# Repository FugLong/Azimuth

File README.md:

<div align="center">

</div>

# Azimuth

Azimuth is a **DIY head tracker** for flight sims, racing, and anything that works with [OpenTrack](https://github.com/opentrack/opentrack). It pairs a small **ESP32** board with a **BNO08x-class** IMU so you get stable orientation without a closed commercial device. This repo has **firmware**, **PCB** designs, **3D** plans, and **documentation**—build it, change it, or fix it yourself.

### Hardware paths

Two supported builds—same core tracker firmware where both apply; use the row that matches what you assembled.

| Path | What it is | Status |
|------|------------|--------|
| **DIY (XIAO + BNO08x)** | **Seeed XIAO ESP32-C3** + **BNO08x** breakout on **SPI** — breadboard or hand-wired. Default **`azimuth_main_diy`**; selected by default in the [**web flasher**](https://fuglong.github.io/Azimuth/). | **Ready** — tracking, Wi‑Fi, portal, USB Hatire, OpenTrack UDP. |
| **Integrated PCB** | [**`kicad/Azimuth_Design`**](kicad/Azimuth_Design/): **ESP32-C3** module, **BNO086**, RGB, buzzer, button. **`azimuth_main_pcb`**; available in the web flasher hardware selector. | **V0.1** — KiCad **ERC/DRC** clean; **assembled boards in hand**, **bring-up and testing in progress**. Same app as DIY — [roadmap](docs/roadmap.md). |

[**docs/wiring.md**](docs/wiring.md) (pinouts) · [**docs/hardware-profiles.md**](docs/hardware-profiles.md) (PlatformIO / GPIO) · [**docs/parts-list.md**](docs/parts-list.md) (sourcing — DIY store links + PCB BOM)

---

### Get started

| | |
|:---|:---|
| **Install or update firmware (USB)** | [**Web flasher**](https://fuglong.github.io/Azimuth/) (**Chrome** / **Edge**). **First flash on a bare custom PCB?** [**Copy/paste USB guide**](docs/first-usb-flash.md) (one time; web/OTA after that). |
| **Update firmware over Wi‑Fi** | Open the portal, hit **Install over Wi‑Fi** in the **Device** card or update banner — *or* hold **FUNC** for ~2 s on the PCB. The chip pulls the latest **official** build from the same GitHub Pages release URL (HTTPS) and reboots into the standby OTA slot. See [**User Guide → Updates**](docs/user-guide.md#9-firmware-updates). |
| **Settings (Wi‑Fi, OpenTrack, device)** | [**http://azimuth.local:8080**](http://azimuth.local:8080) — only after the board is on your home network. First time? Connect to **Azimuth-Tracker** (**Offline Mode**) and follow the [**quick start**](docs/quickstart.md). |
| **Manual (how to use the device)** | [**docs/user-guide.md**](docs/user-guide.md) |
| **Short Wi‑Fi → OpenTrack path** | [**docs/quickstart.md**](docs/quickstart.md) |

---

<div align="center">
<table>
  <tr>
    <td align="center"></td>
    <td align="center"></td>
  </tr>
</table>
</div>

## Overview

- **OpenTrack-first** — Send motion over **Wi‑Fi (UDP)** or **USB (Hatire)**; configure most things in the on-device web UI.
- **Affordable, open stack** — Sensible parts list, KiCad project, and firmware you can build with [PlatformIO](https://platformio.org/).
- **No cloud** — No account or hosted service; setup and tracking stay on your network.
- **Successor** to [Nano33_PC_Head_Tracker](https://github.com/FugLong/Nano33_PC_Head_Tracker): same DIY spirit, but rebuilt around **ESP32** and an external fusion IMU for better results than the old Nano 33 BLE + LSM9DS1 path.

## Need to know

- **Flashing** — Browser install needs **Chrome** or **Edge** (Web Serial). If the installer offers **erase flash**, use it for a clean device (same effect as a full settings reset).
- **First Wi‑Fi setup** — Join **Azimuth-Tracker** (**Offline Mode**), open **`http://192.168.4.1`**, save your home network. Details: [**quick start**](docs/quickstart.md) · full walkthrough: [**User Guide**](docs/user-guide.md).
- **OpenTrack** — Use **either** UDP **or** Hatire as the input, not both at once. Defaults and axis mapping: [**Using Azimuth**](docs/using-azimuth.md#opentrack-on-the-pc).
- **Power, heat, tuning** — Normal for Wi‑Fi on a small module; portal **Tracking & radio** settings; full behavior + battery notes: [**Power, heat, and battery (firmware)**](docs/power-and-thermal.md).

## Documentation

| Doc | Audience |
|-----|----------|
| [**User Guide**](docs/user-guide.md) | **Manual** — Wi‑Fi, portal, FUNC, OpenTrack, updates, battery, troubleshooting |
| [**Quick start**](docs/quickstart.md) | Fast path from flash to tracking over Wi‑Fi |
| [**Using Azimuth**](docs/using-azimuth.md) | Settings portal reference, OpenTrack (USB + Wi‑Fi), tips |
| [**Power, heat, and battery (firmware)**](docs/power-and-thermal.md) | Wi‑Fi power saving, portal polling, defaults; battery runtime / PCB pack polarity |
| [**Development**](docs/development.md) | Building firmware, CI, versioning, repo layout |
| [**Firmware architecture plan**](docs/firmware-architecture-plan.md) | Maintainers — module layout (**network split done**), CI, remaining refactors |
| [**I/O experience plan**](docs/io-led-buzzer-plan.md) | LED / buzzer / FUNC — pause/stasis, layered overrides, **wireless OTA** |
| [**Implementation handoff**](docs/implementation-handoff-prompt.md) | Copy-paste prompt + ordered tasks for agents / new contributors |
| [**Wiring**](docs/wiring.md) · [**Hardware profiles**](docs/hardware-profiles.md) · [**Parts / BOM**](docs/parts-list.md) · [**KiCad**](docs/kicad.md) | Pinouts (DIY + PCB), PlatformIO, BOM, KiCad |
| [**Roadmap**](docs/roadmap.md) | Progress, milestones, future work |
| [**Enclosure (Onshape CAD)**](https://cad.onshape.com/documents/fa78666ff0e219ba32d45d9f/w/679625cc5ba48f8e098cba83/e/0cd4f9cad8e872128d491b46) | Interactive 3D model — print/fit validation still in progress ([roadmap](docs/roadmap.md)) |

## Goals

- **Performance** — Low latency and stable orientation for games and desktop use.
- **Accessibility** — Easy-to-source parts and open tooling so people can build and modify their own trackers.
- **Interop** — First-class support for the same **OpenTrack** pipelines games and sims already use.
- **Evolvability** — Room for better calibration, on-device UX, and companion apps without legacy platform limits.

## Progress (toward V1)

| Area | Progress | Notes |
|------|:--------:|--------|
| Hardware / BOM | 100% | [Parts list](docs/parts-list.md) |
| Azimuth custom PCB ([`Azimuth_Design`](kicad/Azimuth_Design/)) — **V0.1** | **100%** (layout) · **units received** | Assembled boards **under test**. RGB / buzzer / FUNC in firmware for bring-up — see [wiring](docs/wiring.md) / [parts-list](docs/parts-list.md) — [roadmap](docs/roadmap.md) |
| Firmware | ~90% | Tracking + Wi‑Fi + portal + Hatire + **wireless OTA** + modular **`track_network_*`**; **battery ADC** polish and optional **`main`** layering remain — [roadmap](docs/roadmap.md) |
| 3D enclosure | ~90%+ | **Design nearly complete** — [**Onshape CAD (interactive)**](https://cad.onshape.com/documents/fa78666ff0e219ba32d45d9f/w/679625cc5ba48f8e098cba83/e/0cd4f9cad8e872128d491b46); print / fit validation still ahead |

```
Hardware/BOM   [████████████████████] 100%
PCB (V0.1)     [████████████████████] 100% design · boards received · testing
Firmware       [██████████████████░░] ~90%
Enclosure      [██████████████████░░] ~90%+ (design)
```

**Detailed roadmap:** [docs/roadmap.md](docs/roadmap.md)

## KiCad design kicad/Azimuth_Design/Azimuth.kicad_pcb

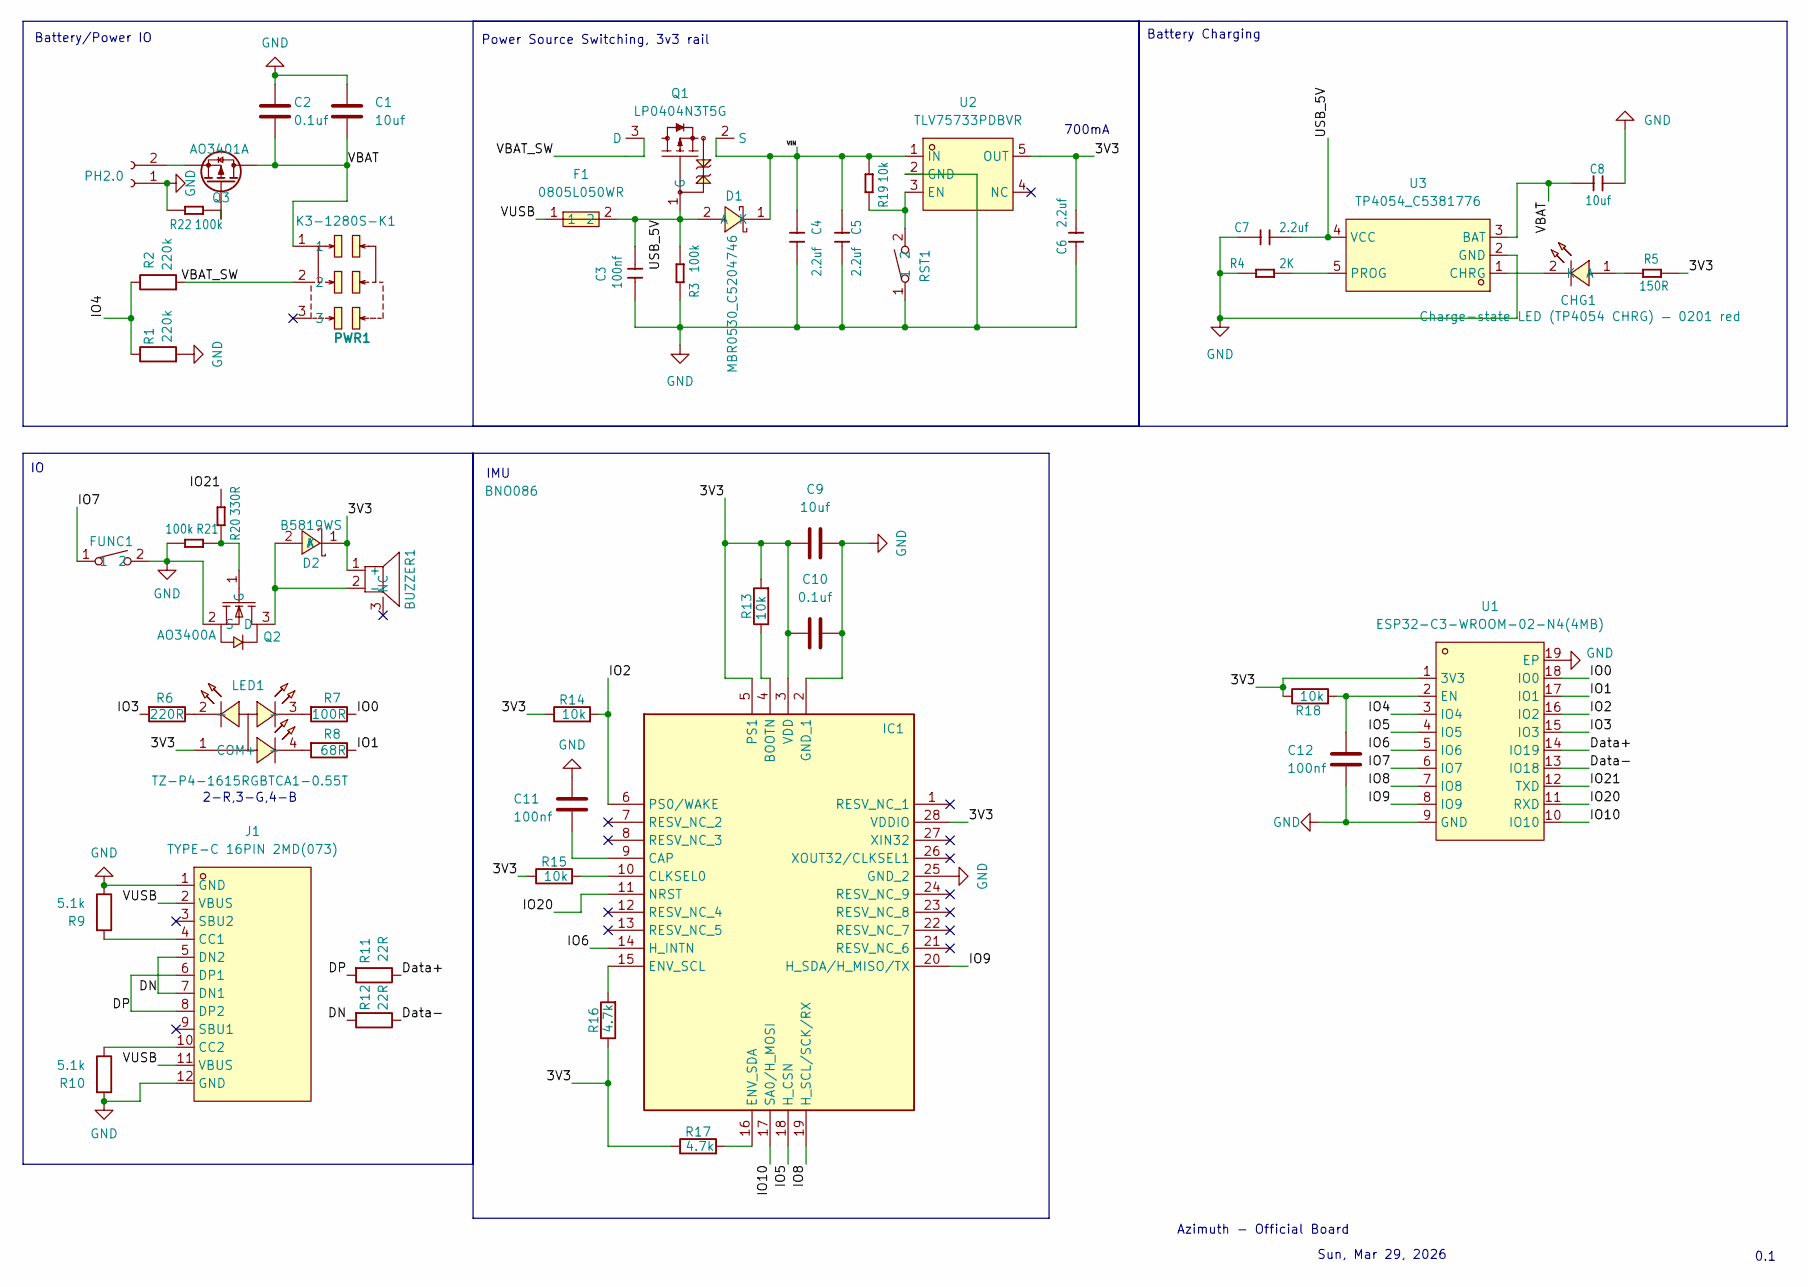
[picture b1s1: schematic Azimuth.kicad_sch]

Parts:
BUZZER1: MLT-5020; BUZ-SMD_L5.0-W5.5-P4.60; Manufacturer_Part_Number MLT-5020; LCSC Part C94598
C1, C8, C9: 10uf; C_0402_1005Metric; Manufacturer_Part_Number CL05A106MP5NUNC; LCSC Part C315248
C2, C10: 0.1uf; C_0402_1005Metric; Manufacturer_Part_Number CC0402KRX7R7BB104; LCSC Part C60474
C3, C11, C12: 100nf; C_0201_0603Metric; Manufacturer_Part_Number GRM033R61A104KE15D; LCSC Part C76934
C4, C5, C6, C7: 2.2uf; C_0201_0603Metric; Manufacturer_Part_Number GRM033R61A225KE47D; LCSC Part C335106
CHG1: XL-0201SURC; LED-SMD_L0.65-W0.35-P0.41_XL-0201SURC; Manufacturer_Part_Number XL-0201SURC; LCSC Part C3646923
D1: MBR0530_C5204746; SOD-123_L2.7-W1.6-LS3.7-RD-1; Manufacturer_Part_Number MBR0530; LCSC Part C5204746
D2: B5819WS; SOD-323_L1.8-W1.3-LS2.5-RD; Manufacturer_Part_Number B5819WS; LCSC Part C64886
F1: 0805L050WR; R0805; Manufacturer_Part_Number 0805L050WR; LCSC Part C207022
FUNC1: HX 3X4X2-2P-1.6N TACTILE SWITCH; KEY-SMD_L4.0-W3.0-LS4.9-1; Manufacturer_Part_Number HX 3x4x2-2P-1.6N TACTILE SWITCH; LCSC Part C49234124
IC1: BNO086; LGA-28_5.2x3.8mm_P0.5mm; Manufacturer_Part_Number BNO086; Mouser Part Number 526-BNO086
J1: TYPE-C 16PIN 2MD(073); USB-C-SMD_TYPE-C-6PIN-2MD-073; LCSC Part C2765186
LED1: TZ-P4-1615RGBTCA1-0.55T; LED-SMD_4P-L1.6-W1.5-BR_TZ-P4-1615; LCSC Part C779813
PH2.0: S2B-PH-SM4-TB(LF)(SN); JST_PH_S2B-PH-SM4-TB_1x02-1MP_P2.00mm_Horizontal; Manufacturer_Part_Number S2B-PH-SM4-TB(LF)(SN); LCSC Part C295747
PWR1: K3-1280S-K1; SW-SMD_K3-1280S-K1; Manufacturer_Part_Number K3-1280S-K1; LCSC Part C128953
Q1: LP0404N3T5G; SOT-883-3_L1.0-W0.6-BR; Manufacturer_Part_Number LP0404N3T5G; LCSC Part C172433
Q2: AO3400A; SOT-23-3_L2.9-W1.3-P1.90-LS2.4-BR; Manufacturer_Part_Number AO3400A; LCSC Part C20917
Q3: AO3401A; SOT-23-3_L2.9-W1.3-P1.90-LS2.4-BR; LCSC Part C347476
R1, R2: 220k; R_0402_1005Metric; Manufacturer_Part_Number 0402WGF2203TCE; LCSC Part C25767
R3, R21, R22: 100k; R_0201_0603Metric; Manufacturer_Part_Number RC0201FR-07100KL; LCSC Part C106224
R4: 2K; R_0201_0603Metric; Manufacturer_Part_Number RC0201FR-072KL; LCSC Part C327392
R5: 150R; R_0201_0603Metric; Manufacturer_Part_Number RC0201FR-07150RL; LCSC Part C295773
R6: 220R; R_0201_0603Metric; Manufacturer_Part_Number GR0201F220RTAG00; LCSC Part C49654383
R7: 100R; R_0201_0603Metric; Manufacturer_Part_Number RC0201FR-07100RL; LCSC Part C77623
R8: 68R; R_0201_0603Metric; Manufacturer_Part_Number GR0201J68RTAG00; LCSC Part C49655823
R9, R10: 5.1k; R_0201_0603Metric; Manufacturer_Part_Number RC0201FR-075K1L; LCSC Part C274341
R11, R12: 22R; R_0201_0603Metric; Manufacturer_Part_Number RC0201FR-0722RL; LCSC Part C155743
R13, R14, R15, R18, R19: 10k; R_0201_0603Metric; Manufacturer_Part_Number RC0201FR-0710KL; LCSC Part C106225
R16, R17: 4.7k; R_0201_0603Metric; Manufacturer_Part_Number RC0201FR-074K7L; LCSC Part C138135
R20: 330R; R_0201_0603Metric; Manufacturer_Part_Number RC0201FR-07330RL; LCSC Part C274872
RST1: HX 3X4X2-2P-1.6N TACTILE SWITCH; KEY-SMD_L4.0-W3.0-LS4.9-1; Manufacturer_Part_Number HX 3x4x2-2P-1.6N TACTILE SWITCH; LCSC Part C49234124
U1: ESP32-C3-WROOM-02-N4(4MB); BULETM-SMD_ESPRESSIF_ESP32-C3-WROOM-02-N4-4MB; LCSC Part C2934560
U2: TLV75733PDBVR; SOT-23-5_L2.9-W1.6-P0.95-LS2.8-BL; Manufacturer_Part_Number TLV75733PDBVR; LCSC Part C485517
U3: TP4054_C5381776; SOT-23-5_L2.9-W1.6-P0.95-LS2.8-BR; LCSC Part C5381776

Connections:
/3V3: BUZZER1.1 (+), C6.2, C9.2, C10.2, D2.1 (K), IC1.3 (VDD), IC1.5 (PS1), IC1.28 (VDDIO), LED1.1 (COM+), R5.1, R13.2, R14.1, R15.1, R16.1, R17.1, R18.1, U1.1 (3V3), U2.5 (OUT)
/DN: J1.5 (DN2), J1.7 (DN1), R12.2
/DP: J1.6 (DP1), J1.8 (DP2), R11.2
/Data+: R11.1, U1.14 (IO19)
/Data-: R12.1, U1.13 (IO18)
/IO0: R7.1, U1.18 (IO0)
/IO1: R8.1, U1.17 (IO1)
/IO2: IC1.6 (PS0/WAKE), R14.2, U1.16 (IO2)
/IO3: R6.2, U1.15 (IO3)
/IO4: R1.1, R2.1, U1.3 (IO4)
/IO5: IC1.18 (H_CSN), U1.4 (IO5)
/IO6: IC1.14 (H_INTN), U1.5 (IO6)
/IO7: FUNC1.1, U1.6 (IO7)
/IO8: IC1.19 (H_SCL/SCK/RX), U1.7 (IO8)
/IO9: IC1.20 (H_SDA/H_MISO/TX), U1.8 (IO9)
/IO10: IC1.17 (SA0/H_MOSI), U1.10 (IO10)
/IO20: IC1.11 (NRST), U1.11 (RXD)
/IO21: R20.2, U1.12 (TXD)
/USB_5V: C3.2, C7.2, D1.2 (A), F1.2, Q1.1 (G), R3.2, U3.4 (VCC)
/VBAT: C1.2, C2.1, C8.1, PWR1.1, Q3.3 (D), U3.3 (BAT)
/VBAT_SW: PWR1.2, Q1.3 (D), R2.2
/VIN: C4.1, C5.1, D1.1 (K), Q1.2 (S), R19.2, U2.1 (IN)
/VUSB: F1.1, J1.2 (VBUS), J1.11 (VBUS)
GND: C1.1, C2.2, C3.1, C4.2, C5.2, C6.1, C7.1, C8.2, C9.1, C10.1, C11.1, C12.1, FUNC1.2, IC1.2 (GND_1), IC1.25 (GND_2), J1.1 (GND), J1.12 (GND), PH2.0.1, Q2.2 (S), R1.2, R3.1, R4.2, R9.1, R10.2, R21.2, R22.1, RST1.1, U1.9 (GND), U1.19 (EP), U2.2 (GND), U3.2 (GND)
unnamed: BUZZER1.2 (-), D2.2 (A), Q2.3 (D)
unnamed: CHG1.1 (A), R5.2
unnamed: CHG1.2 (K), U3.1 (CHRG)
unnamed: IC1.4 (BOOTN), R13.1
unnamed: C11.2, IC1.9 (CAP)
unnamed: IC1.10 (CLKSEL0), R15.2
unnamed: IC1.15 (ENV_SCL), R16.2
unnamed: IC1.16 (ENV_SDA), R17.2
unnamed: J1.4 (CC1), R9.2
unnamed: J1.10 (CC2), R10.1
unnamed: LED1.2 (-), R6.1
unnamed: LED1.3 (-), R7.2
unnamed: LED1.4 (-), R8.2
unnamed: PH2.0.2, Q3.2 (S)
unnamed: Q2.1 (G), R20.1, R21.1
unnamed: Q3.1 (G), R22.2
unnamed: C12.2, R18.2, U1.2 (EN)
unnamed: R19.1, RST1.2, U2.3 (EN)
unnamed: R4.1, U3.5 (PROG)

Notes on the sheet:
Sun, Mar 29, 2026
0.1
Azimuth - Official Board
IMU
Battery/Power IO
Battery Charging
700mA
Power Source Switching, 3v3 rail
2-R,3-G,4-B

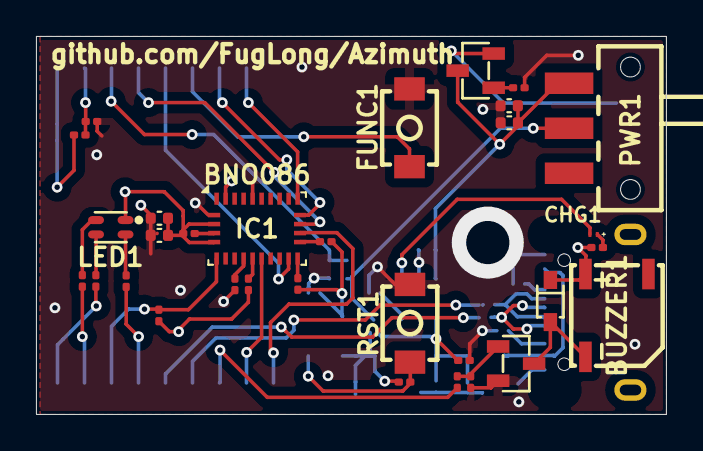
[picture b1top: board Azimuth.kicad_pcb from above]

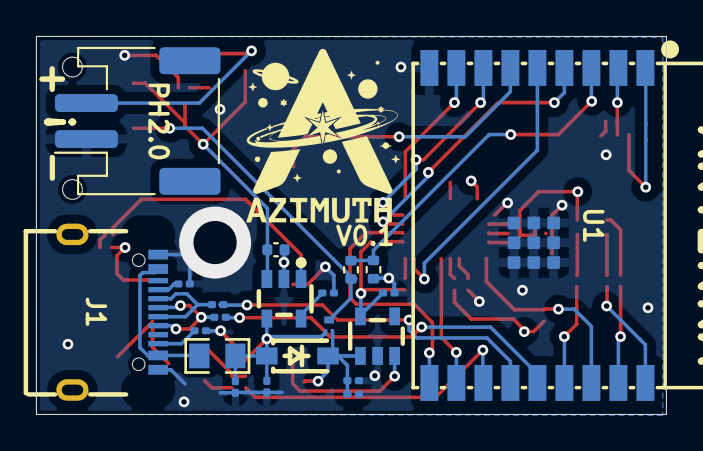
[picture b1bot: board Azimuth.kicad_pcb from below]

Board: 4 copper layers, 35.0 x 21.0 mm, 52 parts (21 on the bottom side), 43 nets.

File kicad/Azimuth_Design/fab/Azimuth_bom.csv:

"Refs","Value","Footprint","LCSC Part","Description","Unit Price (USD)","Qty","DNP"
"BUZZER1","MLT-5020","1_MyFootPrints:BUZ-SMD_L5.0-W5.5-P4.60","C94598","Passive magnetic buzzer: PWM via Q2 low-side switch","0.4246","1",""
"C1","10uf","Capacitor_SMD:C_0402_1005Metric","C315248","VBAT bulk after switch: local energy for TX bursts","0.0087","1",""
"C2","0.1uf","Capacitor_SMD:C_0402_1005Metric","C60474","VBAT switched rail HF bypass at divider / switch node","0.001","1",""
"C3","100nf","Capacitor_SMD:C_0201_0603Metric","C76934","USB_5V (post-fuse VBUS) HF bypass to GND","0.002","1",""
"C4","2.2uf","Capacitor_SMD:C_0201_0603Metric","C335106","Bypass: LDO input / charger adjacent 2.2 µF ceramic (0201)","0.0212","1",""
"C5","2.2uf","Capacitor_SMD:C_0201_0603Metric","C335106","ESP32-C3 module / 3V3 rail local bypass (per placement)","0.0212","1",""
"C6","2.2uf","Capacitor_SMD:C_0201_0603Metric","C335106","TP4054 VCC bypass","0.0212","1",""
"C7","2.2uf","Capacitor_SMD:C_0201_0603Metric","C335106","TP4054 BAT pin stability / output cap per reference design","0.0212","1",""
"C8","10uf","Capacitor_SMD:C_0402_1005Metric","C315248","LDO input or output bulk (per schematic net)","0.0087","1",""
"C9","10uf","Capacitor_SMD:C_0402_1005Metric","C315248","3V3 bulk decoupling","0.0087","1",""
"C10","0.1uf","Capacitor_SMD:C_0402_1005Metric","C60474","3V3 / LDO output HF decoupling","0.001","1",""
"C11","100nf","Capacitor_SMD:C_0201_0603Metric","C76934","BNO086 CAP pin bypass to GND (datasheet requirement)","0.002","1",""
"C12","100nf","Capacitor_SMD:C_0201_0603Metric","C76934","LDO / 3V3 bypass (per net)","0.002","1",""
"CHG1","XL-0201SURC","1_MyFootPrints:LED-SMD_L0.65-W0.35-P0.41_XL-0201SURC","C3646923","Charge-state LED (TP4054 CHRG) — 0201 red","0.069","1",""
"D1","MBR0530_C5204746","1_MyFootPrints:SOD-123_L2.7-W1.6-LS3.7-RD-1","C5204746","Schottky (30 V / 0.5 A class): ORing / clamp in VBAT–LDO path with Q1 per schematic","0.0193","1",""
"D2","B5819WS","1_MyFootPrints:SOD-323_L1.8-W1.3-LS2.5-RD","C64886","Passive buzzer flyback Schottky: cathode to 3V3/+buzzer, anode to Q2 drain","0.0217","1",""
"F1","0805L050WR","1_MyFootPrints:R0805","C207022","PTC resettable fuse ~500 mA hold on battery feed (matches charge budget)","0.1119","1",""
"FUNC1","HX 3X4X2-2P-1.6N TACTILE SWITCH","1_MyFootPrints:KEY-SMD_L4.0-W3.0-LS4.9-1","C49234124","User button: FUNC to GND, IO7 with internal pull-up","0.0186","1",""
"IC1","BNO086","Package_LGA:LGA-28_5.2x3.8mm_P0.5mm","","9-axis fusion IMU (accel/gyro/mag); SPI to ESP32; straps per schematic","11.50","1",""
"J1","TYPE-C 16PIN 2MD(073)","1_MyFootPrints:USB-C-SMD_TYPE-C-6PIN-2MD-073","C2765186","USB-C receptacle: VBUS, GND, D+/D− (6-pin footprint)","0.0649","1",""
"LED1","TZ-P4-1615RGBTCA1-0.55T","rgb_led_C779813:LED-SMD_4P-L1.6-W1.5-BR_TZ-P4-1615","C779813","1615 RGB common-anode: cathodes via R6–R8; active-low drive on IO0/1/3","0.0244","1",""
"PH2.0","S2B-PH-SM4-TB(LF)(SN)","Connector_JST:JST_PH_S2B-PH-SM4-TB_1x02-1MP_P2.00mm_Horizontal","C295747","1S LiPo JST-PH battery connector (horizontal SMD)","0.1947","1",""
"PWR1","K3-1280S-K1","1_MyFootPrints:SW-SMD_K3-1280S-K1","C128953","Slide switch: battery disconnect / power control","0.1791","1",""
"Q1","LP0404N3T5G","1_MyFootPrints:SOT-883-3_L1.0-W0.6-BR","C172433","Power OR / ideal-diode style switch: VBAT vs VUSB path into LDO input","0.0267","1",""
"Q2","AO3400A","1_MyFootPrints:SOT-23-3_L2.9-W1.3-P1.90-LS2.4-BR","C20917","NMOS low-side: PWM buzzer − terminal; Id rating >> buzzer current","0.0798","1",""
"Q3","AO3401A","1_MyFootPrints:SOT-23-3_L2.9-W1.3-P1.90-LS2.4-BR","C347476","PMOS reverse-polarity protection on battery input: source from JST+, drain to VBAT rail","0.0311","1",""
"R1","220k","Resistor_SMD:R_0402_1005Metric","C25767","Battery divider high side: VBAT_SW to ADC tap on IO4 (with R2)","0.0007","1",""
"R2","220k","Resistor_SMD:R_0402_1005Metric","C25767","Battery divider low side: VBAT_SW tap to IO4 for ADC (with R1)","0.0007","1",""
"R3","100k","Resistor_SMD:R_0201_0603Metric","C106224","Power path bias / discharge (Q1 gate network per schematic)","0.001","1",""
"R4","2K","Resistor_SMD:R_0201_0603Metric","C327392","TP4054 PROG: sets IBAT ≈ 500 mA (1000/R_kΩ mA)","0.0011","1",""
"R5","150R","Resistor_SMD:R_0201_0603Metric","C295773","CHG1 current limit: red charge indicator from 3V3","0.0011","1",""
"R6","220R","Resistor_SMD:R_0201_0603Metric","C49654383","RGB LED blue cathode resistor (IO3); tuned with R7/R8 for TZ-P4-1615RGBTCA1 balance on 3V3","0.0006","1",""
"R7","100R","Resistor_SMD:R_0201_0603Metric","C77623","RGB LED red cathode resistor (IO0)","0.0011","1",""
"R8","68R","Resistor_SMD:R_0201_0603Metric","C49655823","RGB LED green cathode resistor (IO1)","0.001","1",""
"R9","5.1k","Resistor_SMD:R_0201_0603Metric","C274341","USB-C CC1 pulldown (Rd)","0.0011","1",""
"R10","5.1k","Resistor_SMD:R_0201_0603Metric","C274341","USB-C CC2 pulldown (Rd) for default current advertisement","0.0011","1",""
"R11","22R","Resistor_SMD:R_0201_0603Metric","C155743","USB D+ series resistor between module and connector","0.0011","1",""
"R12","22R","Resistor_SMD:R_0201_0603Metric","C155743","USB D− series resistor between module and connector","0.0011","1",""
"R13","10k","Resistor_SMD:R_0201_0603Metric","C106225","BNO086 strap (NRST/BOOT network per schematic)","0.0011","1",""
"R14","10k","Resistor_SMD:R_0201_0603Metric","C106225","PS0/WAKE pull-up to 3V3 on IO2 (BNO086 SPI strap + ESP32 GPIO2)","0.0011","1",""
"R15","10k","Resistor_SMD:R_0201_0603Metric","C106225","BNO086 CLKSEL0 pull-up to 3V3","0.0011","1",""
"R16","4.7k","Resistor_SMD:R_0201_0603Metric","C138135","BNO086 strap / support network (per schematic)","0.001","1",""
"R17","4.7k","Resistor_SMD:R_0201_0603Metric","C138135","BNO086 strap / support network (per schematic)","0.001","1",""
"R18","10k","Resistor_SMD:R_0201_0603Metric","C106225","Power control: TLV75733 EN / divider network (see schematic nets)","0.0011","1",""
"R19","10k","Resistor_SMD:R_0201_0603Metric","C106225","Power control: TLV75733 EN / divider network (see schematic nets)","0.0011","1",""
"R20","330R","Resistor_SMD:R_0201_0603Metric","C274872","Q2 gate series resistor: limits inrush / EMI from IO21","0.0011","1",""
"R21","100k","Resistor_SMD:R_0201_0603Metric","C106224","Q2 NMOS gate discharge to GND (default buzzer off)","0.001","1",""
"R22","100k","Resistor_SMD:R_0201_0603Metric","C106224","Q3 PMOS gate pull-down to GND: keeps reverse-protection FET enhanced with correct battery polarity","0.001","1",""
"RST1","HX 3X4X2-2P-1.6N TACTILE SWITCH","1_MyFootPrints:KEY-SMD_L4.0-W3.0-LS4.9-1","C49234124","Tactile: strap / reset function per schematic","0.0186","1",""
"U1","ESP32-C3-WROOM-02-N4(4MB)","1_MyFootPrints:BULETM-SMD_ESPRESSIF_ESP32-C3-WROOM-02-N4-4MB","C2934560","MCU + RF: Wi-Fi/BLE, USB-OTG PHY, 4 MB flash; Azimuth GPIO map per wiring.md","3.0674","1",""
"U2","TLV75733PDBVR","1_MyFootPrints:SOT-23-5_L2.9-W1.6-P0.95-LS2.8-BL","C485517","3.3 V LDO: up to ~1 A out, low IQ; feeds digital + RF rail","0.1959","1",""
"U3","TP4054_C5381776","1_MyFootPrints:SOT-23-5_L2.9-W1.6-P0.95-LS2.8-BR","C5381776","Linear Li-ion charger from USB_5V; CC/CV, ~500 mA with R4","0.0145","1",""

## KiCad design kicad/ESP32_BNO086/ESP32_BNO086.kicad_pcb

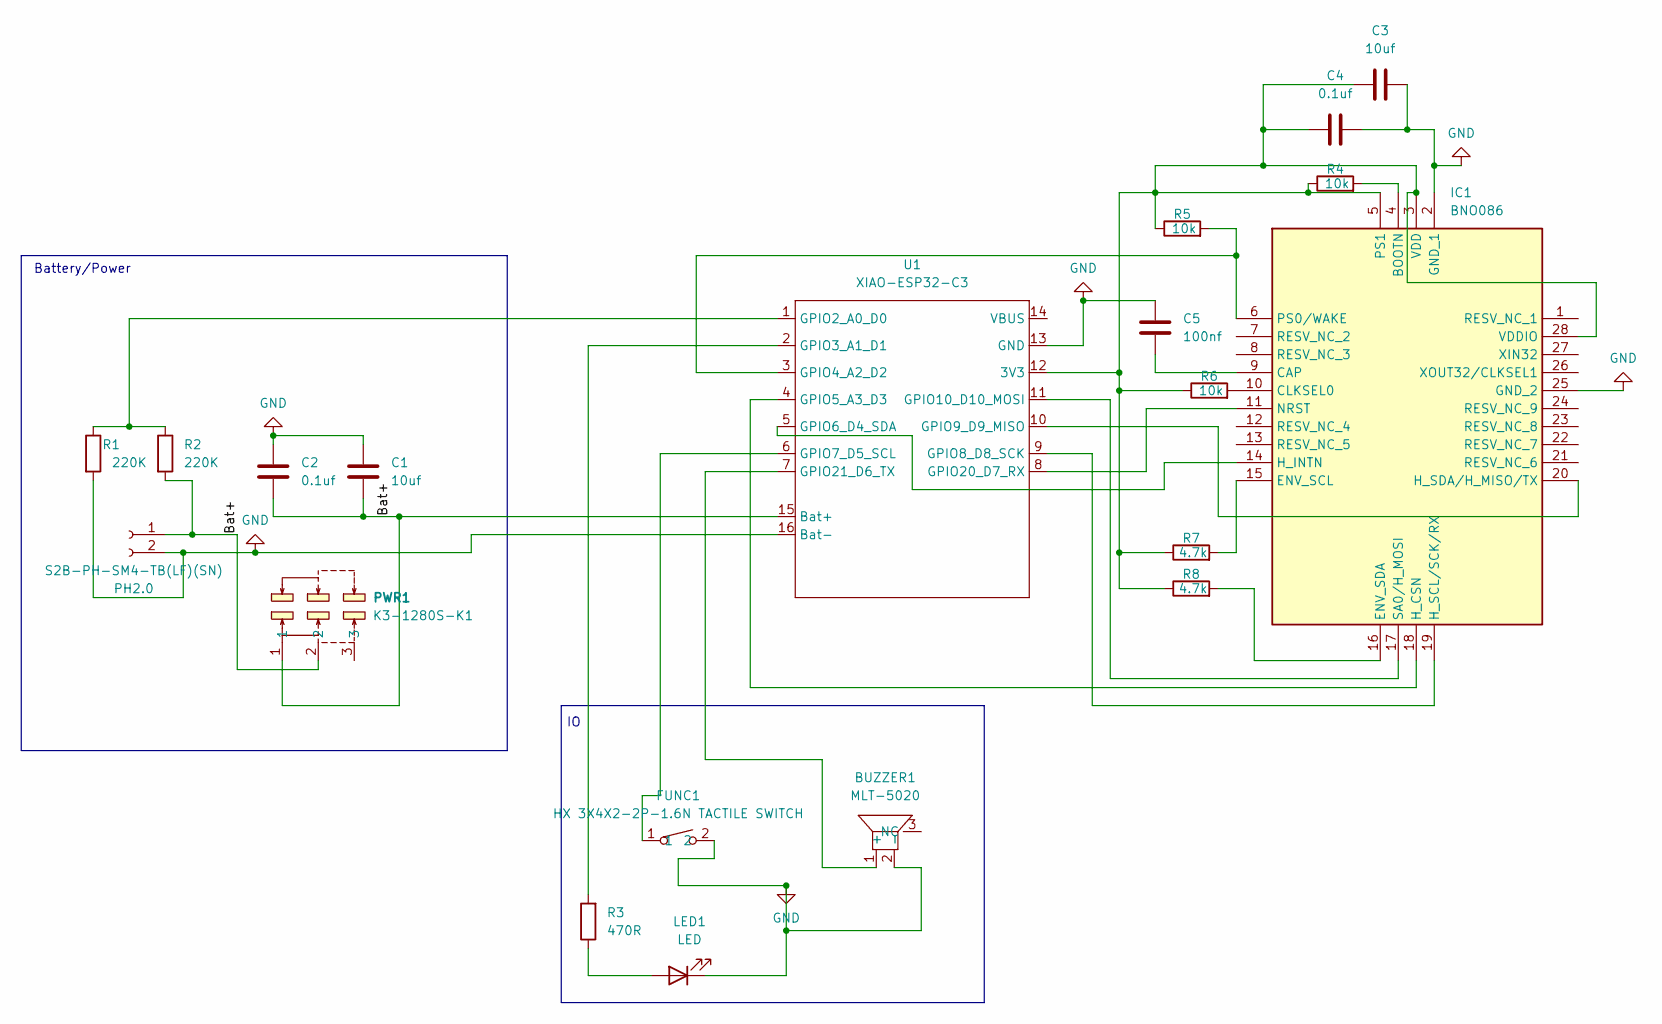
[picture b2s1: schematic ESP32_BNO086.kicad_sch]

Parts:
BUZZER1: MLT-5020; BUZ-SMD_L5.0-W5.5-P4.60; Manufacturer_Part_Number MLT-5020; LCSC Part C94598
C1, C3: 10uf; C_0603_1608Metric; Manufacturer_Part_Number CL10A106KP8NNNC; LCSC Part C19702
C2, C4: 0.1uf; C_0603_1608Metric; Manufacturer_Part_Number CC0603KRX7R9BB104; LCSC Part C14663
C5: 100nf; C_0402_1005Metric; Manufacturer_Part_Number GRM155R71H104KE14D; LCSC Part C77020
FUNC1: HX 3X4X2-2P-1.6N TACTILE SWITCH; KEY-SMD_L4.0-W3.0-LS4.9-1; Manufacturer_Part_Number HX 3x4x2-2P-1.6N TACTILE SWITCH; LCSC Part C49234124
IC1: BNO086; LGA-28_5.2x3.8mm_P0.5mm; Manufacturer_Part_Number BNO086; Mouser Part Number 526-BNO086
LED1: LED; LED_0402_1005Metric; Manufacturer_Part_Number YLED0402R; LCSC Part C21260817
PH2.0: S2B-PH-SM4-TB(LF)(SN); JST_PH_S2B-PH-SM4-TB_1x02-1MP_P2.00mm_Horizontal; Manufacturer_Part_Number S2B-PH-SM4-TB(LF)(SN); LCSC Part C295747
PWR1: K3-1280S-K1; SW-SMD_K3-1280S-K1; Manufacturer_Part_Number K3-1280S-K1; LCSC Part C128953
R1, R2: 220K; R_0603_1608Metric; Manufacturer_Part_Number FRC0603F2203TS; LCSC Part C2907013
R3: 470R; R_0402_1005Metric; Manufacturer_Part_Number RC0402FR-07470RL; LCSC Part C114877
R4, R5, R6: 10k; R_0402_1005Metric; Manufacturer_Part_Number RC0402FR-0710KL; LCSC Part C60490
R7, R8: 4.7k; R_0402_1005Metric; Manufacturer_Part_Number RC0402FR-074K7L; LCSC Part C105871
U1: XIAO-ESP32-C3; XIAO-ESP32-C3-DIP-SMD; Manufacturer_Part_Number 113991054; Mouser Part Number 713-113991054

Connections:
GND: BUZZER1.2 (-), C1.1, C2.2, C3.1, C4.1, C5.1, FUNC1.2, IC1.2 (GND_1), IC1.25 (GND_2), LED1.1 (K), PH2.0.2, R1.2, U1.13 (GND), U1.16 (Bat-)
unnamed: BUZZER1.1 (+), U1.7 (GPIO21_D6_TX)
unnamed: IC1.4 (BOOTN), R4.2
unnamed: C5.2, IC1.9 (CAP)
unnamed: IC1.10 (CLKSEL0), R6.2
unnamed: IC1.15 (ENV_SCL), R7.2
unnamed: IC1.16 (ENV_SDA), R8.2
unnamed: IC1.18 (H_CSN), U1.4 (GPIO5_A3_D3)
unnamed: IC1.14 (H_INTN), U1.5 (GPIO6_D4_SDA)
unnamed: IC1.19 (H_SCL/SCK/RX), U1.9 (GPIO8_D8_SCK)
unnamed: IC1.20 (H_SDA/H_MISO/TX), U1.10 (GPIO9_D9_MISO)
unnamed: IC1.11 (NRST), U1.8 (GPIO20_D7_RX)
unnamed: IC1.6 (PS0/WAKE), R5.2, U1.3 (GPIO4_A2_D2)
unnamed: C3.2, C4.2, IC1.3 (VDD), IC1.5 (PS1), IC1.28 (VDDIO), R4.1, R5.1, R6.1, R7.1, R8.1, U1.12 (3V3)
unnamed: IC1.17 (SA0/H_MOSI), U1.11 (GPIO10_D10_MOSI)
unnamed: LED1.2 (A), R3.1
unnamed: R1.1, R2.1, U1.1 (GPIO2_A0_D0)
unnamed: R3.2, U1.2 (GPIO3_A1_D1)
unnamed: FUNC1.1, U1.6 (GPIO7_D5_SCL)

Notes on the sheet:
Battery/Power

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
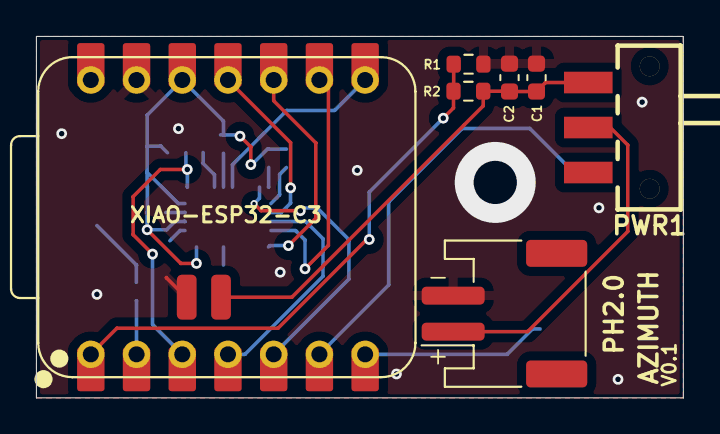
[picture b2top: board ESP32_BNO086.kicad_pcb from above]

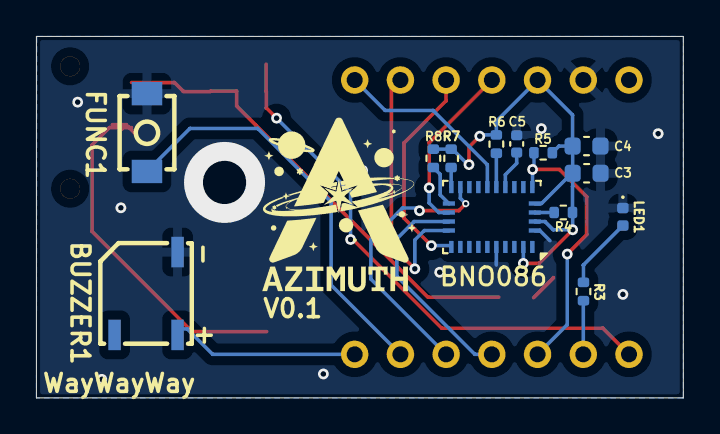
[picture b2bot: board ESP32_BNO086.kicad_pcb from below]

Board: 2 copper layers, 35.9 x 20.1 mm, 20 parts (13 on the bottom side), 21 nets.

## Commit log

2026-03-22 Initial commit: ESP32-C3 BNO08x head tracking firmware
    - PlatformIO firmware for Seeed XIAO ESP32-C3 + BNO08x (SPI)
    - Debug and Hatire (OpenTrack) build targets
    - Wiring documentation for XIAO ↔ BNO08x
    Made-with: Cursor
2026-03-22 readme tweaks
2026-03-22 Added kicad files for custom PCB (WIP)
2026-03-22 Added kicad libs, 3d models + updated paths
2026-03-22 Readme refinements/updates
2026-03-22 roadmap added
2026-03-22 wiring changes
2026-03-23 Updated PCB design
2026-03-23 PCB tweaks again
2026-03-23 Created V1 gerber files and BOM, still WIP
2026-03-24 pcb updates, doc updates, lib updates
2026-03-26 Logo added, doc updates, board tweaks, imgs
2026-03-27 Hatire small bugfix
2026-03-27 Wifi UDP implemented, settings secrets file for now
2026-03-27 mapping fixes, readme update
2026-03-28 Wifi optimization + more
2026-03-28 Settings UI added
2026-03-28 logo added to settings
2026-03-28 updated settings and setup, logo converted
2026-03-28 portal update, new settings
2026-03-28 Settings QOL improvements
2026-03-28 axis mappings and inversions added to settings
2026-03-28 Web tool flash page, CICD
2026-03-28 flasher page update
2026-03-28 flash page tweaks
2026-03-28 tiny cleanup
2026-03-28 user facing language/UX fixes
2026-03-28 More UX language refinement
2026-03-28 flasher wording tweaks, quickstart added
2026-03-28 hopefully last UX refinement for flasher
2026-03-28 portal reset to default refinement
2026-03-28 update checker, version numbers
2026-03-28 Readme updates
2026-03-28 complete readme refactor, doc updates
2026-03-28 battery added to parts list
2026-03-29 okay redoing the whole PCB, yes I am insane
2026-03-30 new offical azimuth PCB design started, big doc updates
2026-03-30 hardware paths refinement
2026-03-30 schematic fixes
2026-03-30 big docs refinement
2026-03-30 readme adding parts list
2026-04-03 new PCB design almost done, big doc update
2026-04-05 PCB locked in for now, docs updated
2026-04-05 Bat updates
2026-04-07 PCB finalized? :O
2026-04-08 Doc cleanup, BOM update
2026-04-08 Manufacturing optimizations
2026-04-18 PCB V0.1 ordered!
2026-05-01 Boards came in! new flashing option in web UI
2026-05-02 web flasher fix hopefully
2026-05-02 gitignore fixes
2026-05-02 goofy tip cleanup
2026-05-02 flasher test fix
2026-05-02 flash script
2026-05-02 0.2.0 Update
    Built out IO for custom PCB, testing underway. All signs point to green!! Batteries coming in soon
2026-05-02 Doc updates
2026-05-02 RGB LED FIX
2026-05-02 actual RGB LED fix
2026-05-02 LED brightness, buzzer volume controls
2026-05-02 light and volume ui update
2026-05-02 start-up chime
2026-05-05 thermal safety, status widgets
2026-05-07 Portal refinement, bat monitoring improvements
2026-05-07 LED controls, integrations, pause functionality, low power mode
2026-05-07 big networking refactor, testing update
2026-05-07 network refactor, UI update
2026-05-09 ui fixes, pose visualizer
2026-05-10 wireless updates
2026-05-10 wireless update changes
2026-05-10 Wireless update system done
2026-05-10 doc update, minor networking tweaks
2026-05-10 doc refresh, new user guide added
2026-05-10 enclosure add
2026-05-10 Logo fix
2026-05-10 Oops, fixed the logo
2026-05-10 Version update
2026-05-10 logo image optimizations
2026-05-12 dynamic loop rate option
2026-05-19 defaults updated, variable loop rate added
2026-05-31 flasher script
2026-05-31 script fix
